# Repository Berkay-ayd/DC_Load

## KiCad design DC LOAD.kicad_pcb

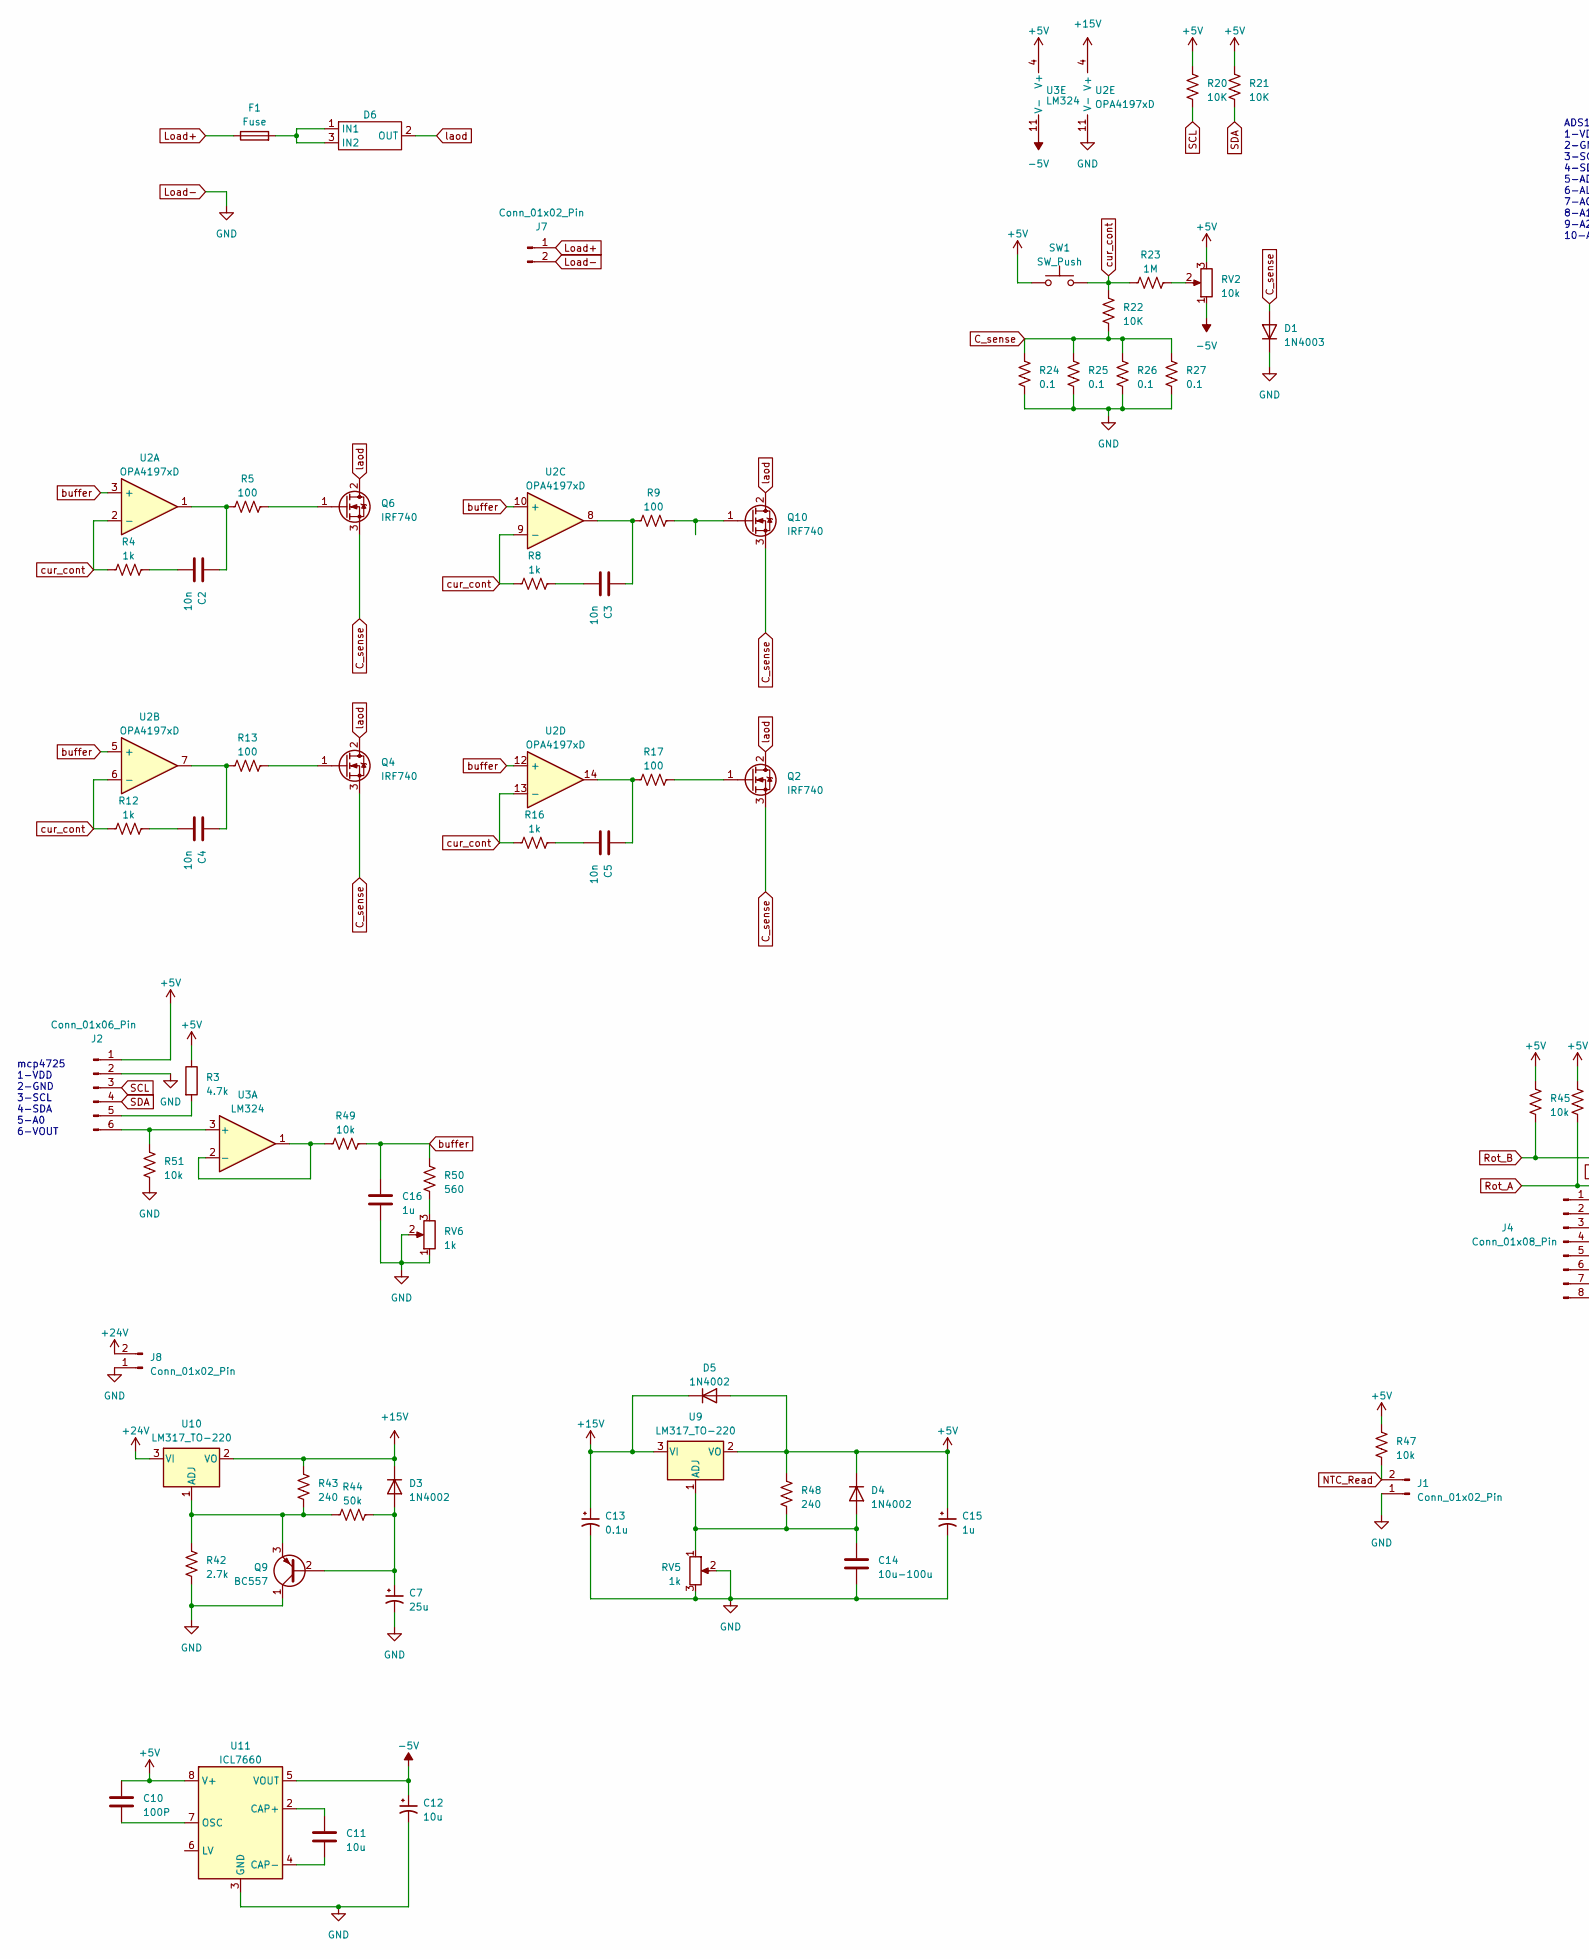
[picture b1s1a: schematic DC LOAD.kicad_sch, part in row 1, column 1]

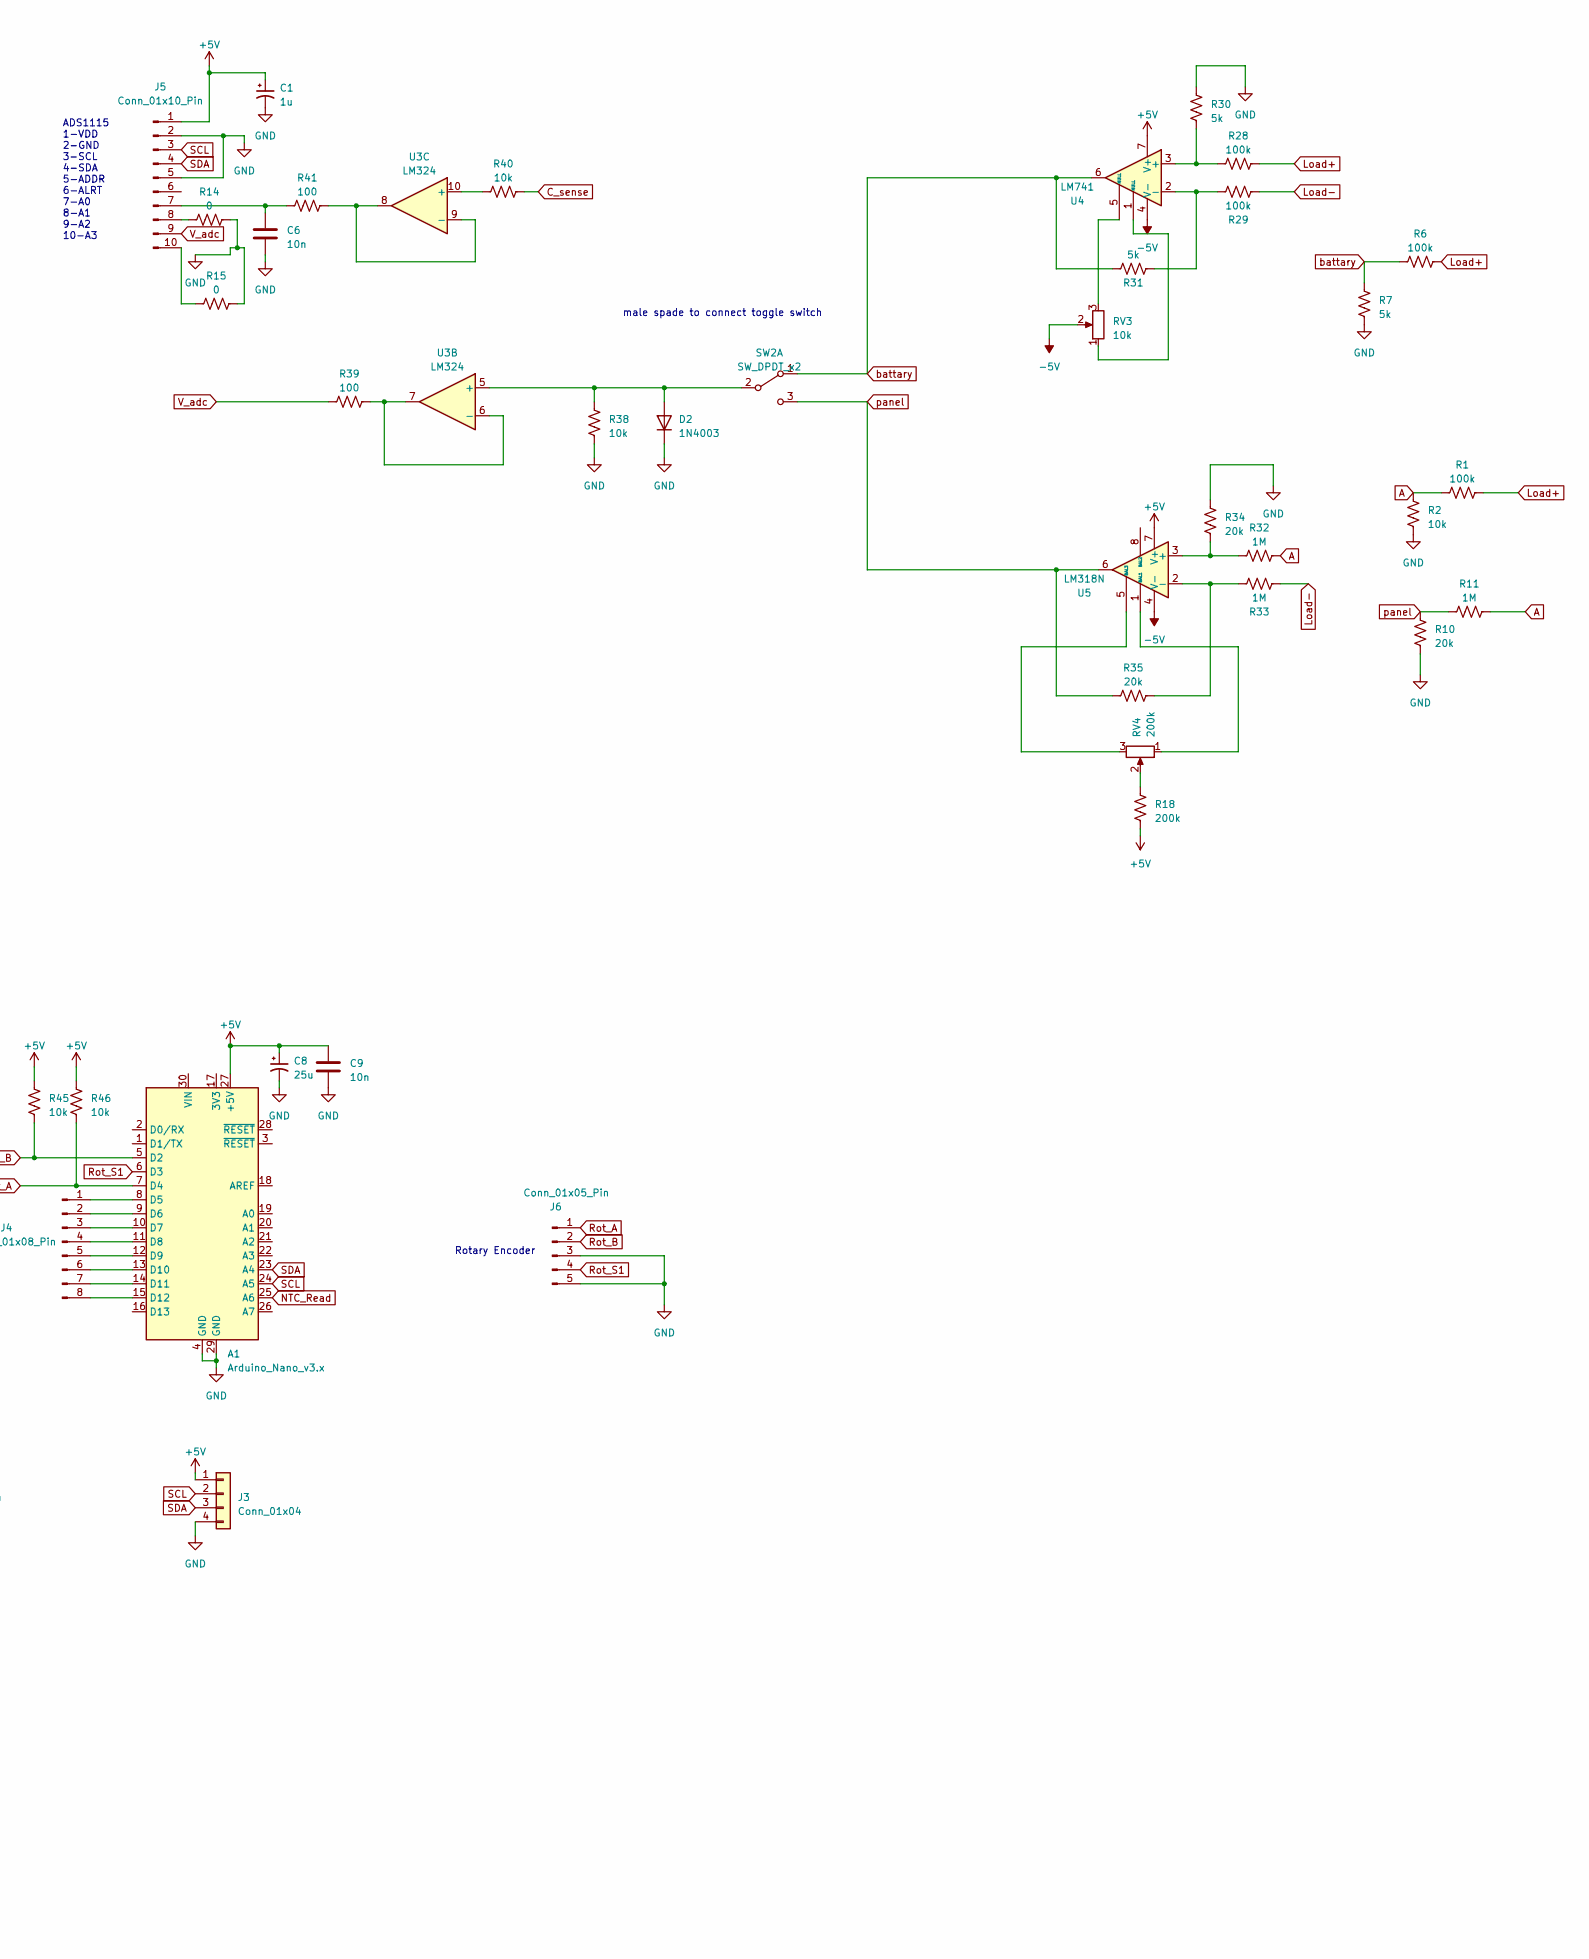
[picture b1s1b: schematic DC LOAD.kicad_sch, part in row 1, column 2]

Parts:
A1: Arduino_Nano_v3.x; Arduino_Nano
C1, C15: 1u; CP_Radial_D8.0mm_P3.50mm
C2, C3, C4, C5, C6, C9: 10n; C_0805_2012Metric
C7, C8: 25u; CP_Radial_D8.0mm_P3.50mm
C10: 100P; C_0805_2012Metric
C11: 10u; C_0805_2012Metric
C12: 10u; CP_Radial_D8.0mm_P3.50mm
C13: 0.1u; C_0805_2012Metric
C14: 10u-100u; C_0805_2012Metric
C16: 1u; C_0805_2012Metric
D1, D2: 1N4003; D_DO-41_SOD81_P10.16mm_Horizontal
D3, D4, D5: 1N4002; D_DO-41_SOD81_P10.16mm_Horizontal
D6: MRB2040
F1: Fuse; Fuseholder_Cylinder-5x20mm_Schurter_0031_8201_Horizontal_Op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
J1, J8: Conn_01x02_Pin; JST_EH_B2B-EH-A_1x02_P2.50mm_Vertical
J2: Conn_01x06_Pin; PinSocket_1x06_P2.54mm_Vertical
J3: Conn_01x04; PinSocket_1x04_P2.54mm_Vertical
J4: Conn_01x08_Pin; PinSocket_1x08_P2.54mm_Vertical
J5: Conn_01x10_Pin; PinSocket_1x10_P2.54mm_Vertical
J6: Conn_01x05_Pin; PinSocket_1x05_P2.54mm_Vertical
J7: Conn_01x02_Pin; Banana_Jack_2Pin
Q2, Q4, Q6, Q10: IRF740; TO-220-3_Vertical
Q9: BC557; TO-92_Inline
R1: 100k; R_Axial_DIN0411_L9.9mm_D3.6mm_P5.08mm_Vertical
R2: 10k; R_Axial_DIN0411_L9.9mm_D3.6mm_P5.08mm_Vertical
R3: 4.7k; R_0805_2012Metric
R4, R8, R12, R16: 1k; R_0805_2012Metric
R5, R9, R13, R17: 100; R_Axial_DIN0207_L6.3mm_D2.5mm_P10.16mm_Horizontal
R6, R28, R29: 100k; R_0805_2012Metric
R7, R30, R31: 5k; R_0805_2012Metric
R10, R34, R35: 20k; R_Axial_DIN0411_L9.9mm_D3.6mm_P5.08mm_Vertical
R11, R32, R33: 1M; R_Axial_DIN0411_L9.9mm_D3.6mm_P5.08mm_Vertical
R14, R15: 0; R_0805_2012Metric
R18: 200k; R_0805_2012Metric
R20, R21: 10K; R_0805_2012Metric
R22: 10K; R_Axial_DIN0204_L3.6mm_D1.6mm_P7.62mm_Horizontal
R23: 1M; R_Axial_DIN0204_L3.6mm_D1.6mm_P7.62mm_Horizontal
R24, R25, R26, R27: 0.1; R_Axial_DIN0614_L14.3mm_D5.7mm_P20.32mm_Horizontal
R38, R40: 10k; R_Axial_DIN0207_L6.3mm_D2.5mm_P10.16mm_Horizontal
R39, R41: 100; R_0805_2012Metric
R42: 2.7k; R_Axial_DIN0207_L6.3mm_D2.5mm_P10.16mm_Horizontal
R43, R48: 240; R_Axial_DIN0207_L6.3mm_D2.5mm_P10.16mm_Horizontal
R44: 50k; R_Axial_DIN0207_L6.3mm_D2.5mm_P10.16mm_Horizontal
R45, R46, R47, R49, R51: 10k; R_0805_2012Metric
R50: 560; R_0805_2012Metric
RV2, RV3: 10k; Potentiometer_Bourns_3299W_Vertical
RV4: 200k; Potentiometer_Bourns_3299W_Vertical
RV5, RV6: 1k; Potentiometer_Bourns_3299W_Vertical
SW1: SW_Push; JST_EH_B2B-EH-A_1x02_P2.50mm_Vertical
SW2: SW_DPDT_x2; JST_EH_B3B-EH-A_1x03_P2.50mm_Vertical
U2: OPA4197xD; DIP-14_W7.62mm
U3: LM324; DIP-14_W7.62mm_Socket
U4: LM741; DIP-8_W7.62mm
U5: LM318N; DIP-8_W7.62mm
U9, U10: LM317_TO-220; TO-220-3_Vertical
U11: ICL7660; DIP-8_W7.62mm

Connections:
+5V: A1.27 (+5V), C1.1, C8.1, C9.1, C10.1, C15.1, D4.1 (K), D5.2 (A), J2.1, J3.1, J5.1, R3.1, R18.2, R20.1, R21.2, R45.1, R46.1, R47.1, R48.2, RV2.3, SW1.1, U3.4 (V+), U4.7 (V+), U5.7 (V+), U9.2 (VO), U11.8 (V+)
+15V: C13.1, D3.1 (K), D5.1 (K), R43.2, U2.4 (V+), U9.3 (VI), U10.2 (VO)
+24V: J8.2, U10.3 (VI)
-5V: C12.1, RV2.1, RV3.2, U3.11 (V-), U4.4 (V-), U5.4 (V-), U11.5 (VOUT)
A: R1.1, R2.1, R11.2, R32.1
C_sense: D1.2 (A), Q2.3 (S), Q4.3 (S), Q6.3 (S), Q10.3 (S), R22.1, R24.2, R25.2, R26.2, R27.2, R40.1
Load+: F1.1, J7.1, R1.2, R6.1, R28.1
Load-: A1.4 (GND), A1.29 (GND), C1.2, C6.2, C7.2, C8.2, C9.2, C12.2, C13.2, C14.2, C15.2, C16.2, D1.1 (K), D2.1 (K), J1.1, J2.2, J3.4, J5.2, J5.5, J6.3, J6.5, J7.2, J8.1, Q9.1 (C), R2.2, R7.2, R10.2, R14.1, R15.1, R24.1, R25.1, R26.1, R27.1, R29.1, R30.1, R33.1, R34.1, R38.1, R42.1, R51.2, RV5.2, RV5.3, RV6.1, RV6.2, U2.11 (V-), U11.3 (GND)
NTC_Read: A1.25 (A6), J1.2, R47.2
unnamed: A1.8 (D5), J4.1
unnamed: A1.9 (D6), J4.2
unnamed: A1.10 (D7), J4.3
unnamed: A1.11 (D8), J4.4
unnamed: A1.12 (D9), J4.5
unnamed: A1.13 (D10), J4.6
unnamed: A1.14 (D11), J4.7
unnamed: A1.15 (D12), J4.8
unnamed: C2.1, R5.1, U2.1
unnamed: C2.2, R4.2
unnamed: C3.1, R9.1, U2.8
unnamed: C3.2, R8.2
unnamed: C4.1, R13.1, U2.7
unnamed: C4.2, R12.2
unnamed: C5.1, R17.1, U2.14
unnamed: C5.2, R16.2
unnamed: D2.2 (A), R38.2, SW2.2 (B), U3.5 (+)
unnamed: C7.1, D3.2 (A), Q9.2 (B), R44.1
unnamed: C14.1, D4.2 (A), R48.1, RV5.1, U9.1 (ADJ)
unnamed: D6.1 (IN1), D6.3 (IN2), F1.2
unnamed: J2.5, R3.2
unnamed: J2.6, R51.1, U3.3 (+)
unnamed: C6.1, J5.7, R41.2
unnamed: J5.8, R14.2
unnamed: J5.10, R15.2
unnamed: Q2.1 (G), R17.2
unnamed: Q4.1 (G), R13.2
unnamed: Q6.1 (G), R5.2
unnamed: Q9.3 (E), R42.2, R43.1, R44.2, U10.1 (ADJ)
unnamed: Q10.1 (G), R9.2
unnamed: R18.1, RV4.2
unnamed: R23.1, RV2.2
unnamed: R50.2, RV6.3
unnamed: RV3.1, U4.1 (NULL)
unnamed: RV3.3, U4.5 (NULL)
unnamed: R49.1, U3.1, U3.2 (-)
unnamed: R39.1, U3.6 (-), U3.7
unnamed: R40.2, U3.10 (+)
unnamed: R41.1, U3.8, U3.9 (-)
unnamed: R28.2, R30.2, U4.3 (+)
unnamed: R29.2, R31.2, U4.2 (-)
unnamed: R32.2, R34.2, U5.3 (+)
unnamed: R33.2, R35.1, U5.2 (-)
unnamed: RV4.1, U5.1 (BAL1)
unnamed: RV4.3, U5.5 (BAL3)
unnamed: C11.1, U11.2 (CAP+)
unnamed: C11.2, U11.4 (CAP-)
unnamed: C10.2, U11.7 (OSC)
Rot_A: A1.7 (D4), J6.1, R46.2
Rot_B: A1.5 (D2), J6.2, R45.2
Rot_S1: A1.6 (D3), J6.4
SCL: A1.24 (A5), J2.3, J3.2, J5.3, R20.2
SDA: A1.23 (A4), J2.4, J3.3, J5.4, R21.1
V_adc: J5.9, R39.2
battary: R6.2, R7.1, R31.1, SW2.1 (A), U4.6
buffer: C16.1, R49.2, R50.1, U2.3 (+), U2.5 (+), U2.10 (+), U2.12 (+)
cur_cont: R4.1, R8.1, R12.1, R16.1, R22.2, R23.2, SW1.2, U2.2 (-), U2.6 (-), U2.9 (-), U2.13 (-)
laod: D6.2 (OUT), Q2.2 (D), Q4.2 (D), Q6.2 (D), Q10.2 (D)
panel: R10.1, R11.1, R35.2, SW2.3 (C), U5.6

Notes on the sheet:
Rotary Encoder
mcp4725 1-VDD 2-GND 3-SCL 4-SDA 5-A0 6-VOUT
ADS1115 1-VDD 2-GND 3-SCL 4-SDA 5-ADDR 6-ALRT 7-A0 8-A1 9-A2 10-A3
male spade to connect toggle switch

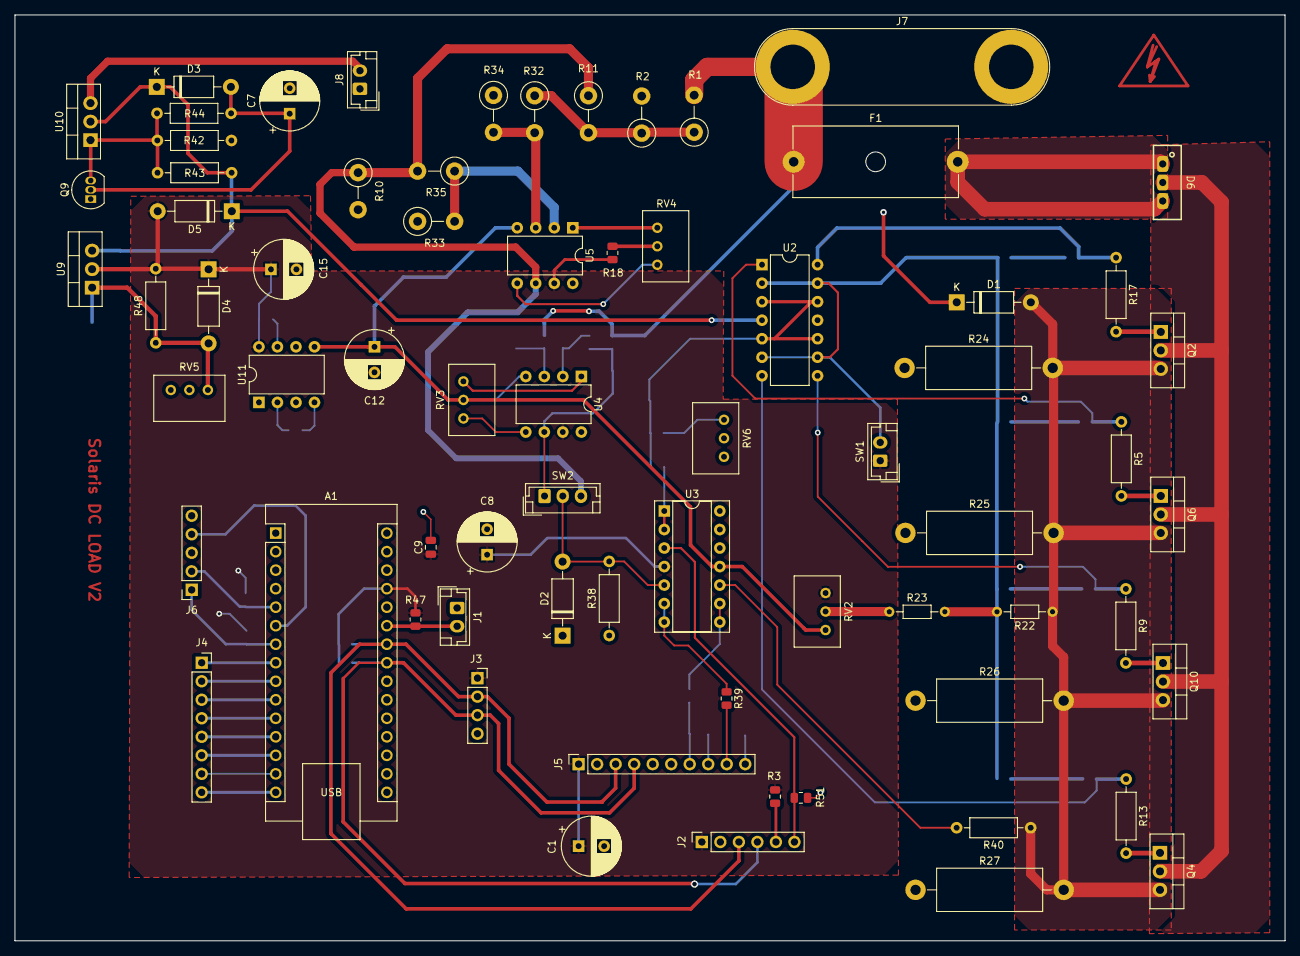
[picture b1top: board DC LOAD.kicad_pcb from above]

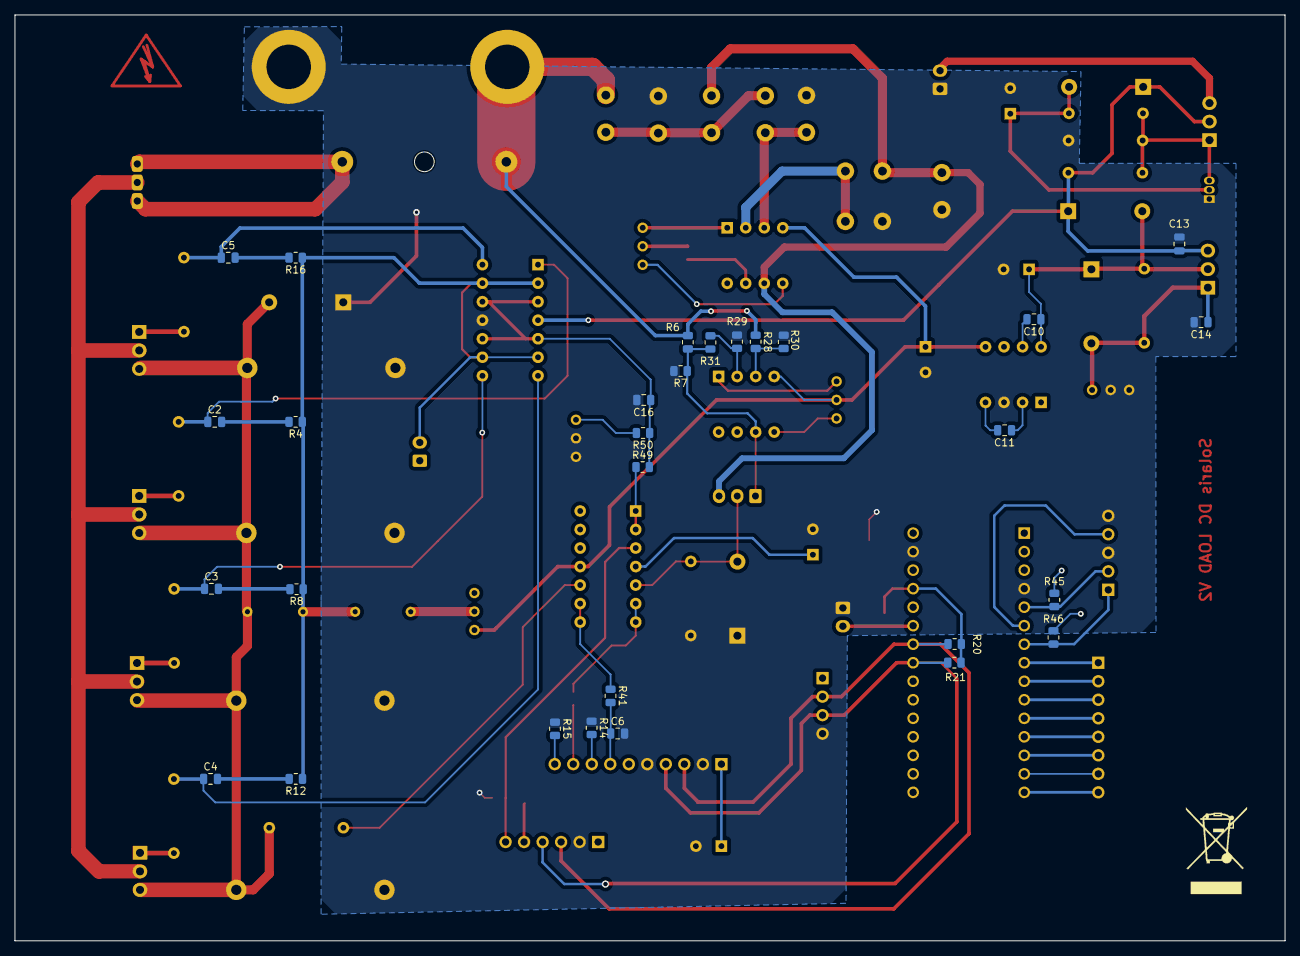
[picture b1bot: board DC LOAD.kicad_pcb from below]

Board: 2 copper layers, 174.2 x 127.0 mm, 99 parts (29 on the bottom side), 68 nets.
